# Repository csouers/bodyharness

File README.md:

# bodyharness
## Expand your openpilot experience with access to your vehicle's chassis CAN bus

Available for purchase at https://autofocuser.com!

This hardware, together with the necessary software and vehicle architecture, makes it possible to electronically control turn signals, door locks, and more. Future software will support features such as low fuel warnings, unlocked vehicle notifications, and headlights on during comma prime snapshots.

Currently, a comma.ai panda (white or grey) is the only required accessory. The black panda can be supported with additional effort (no plans for this at the moment). The supported pandas have 3 CAN bus transceivers, k-line and l-line connections, and a single GMLAN connection (operates in place of one of the panda's CAN bus connections). Future hardware revisions will support LIN (k-line and l-line).

## Compatibility
##### Based on vehicle generation. Vehicles may vary. Check your car first!
| Make | Model | B-CAN Connection Location |
| -- | -- | -- |
| Acura     | ILX 2016-18                   | TBD                                                                                          |
| Acura     | RDX 2016-18                   | TBD                                                                                          |
| Honda     | Accord 2018-21                | Option Connector (Pinout A) PINK 2+ / BLUE 3-                                                |
| Honda     | Accord Hybrid 2018-21         | Option Connector (Pinout A) PINK 2+ / BLUE 3-                                                |
| Honda     | Clarity 2017-21               | Option Connector (Pinout A) PINK 2+ / BLUE 3-                                                |
| Honda     | Civic Hatchback 2017-21       | Option Connector (Pinout A) PINK 2+ / BLUE 3-                                                |
| Honda     | Civic Sedan/Coupe 2016-21     | Option Connector (Pinout A) PINK 2+ / BLUE 3-                                                |
| Honda     | CR-V 2015-16                  | (DIY) at BCM/Under Dash Fuse Box or other module                                             |
| Honda     | CR-V 2017-21                  | Option Connector (Pinout A) PINK 2+ / BLUE 3-                                                |                                              
| Honda     | CR-V Hybrid 2017-2021         | Option Connector (Pinout A) PINK 2+ / BLUE 3-                                                |
| Honda     | Fit 2018-19                   | (DIY) 2018 at BCM/Under Dash Fuse/Relay Box or other module - 2019+ at ADAS Camera Connector |
| Honda     | HR-V 2019-2021                | (DIY) at ADAS Camera Connector                                                               |
| Honda     | Insight 2019-21               | (DIY) at BCM/Under Dash Fuse/Relay Box or other module                                       |
| Honda     | Odyssey 2018-21               | Option Connector (Pinout B) PINK 2+ / BLUE 5-                                                |
| Honda     | Passport 2019-21              | (DIY) BCM/Under Dash Fuse/Relay Box or other module - 2020+ at ADAS Camera Connector         |
| Honda     | Pilot 2016-21                 | (DIY) BCM/Under Dash Fuse/Relay or other module - 2019+ at ADAS Camera Connector             |
| Honda     | Ridgeline 2017-21             | (DIY) BCM/Under Dash Fuse/Relay or other module - 2020+ at ADAS Camera Connector             |

As usual, anything on this repository is to be used AT YOUR OWN RISK! You maintain all liability.
<!--stackedit_data:
eyJoaXN0b3J5IjpbMTAyMDg2MzIxNCw4MjI2NDQ3OTEsLTk1Nj
MwMjA3NiwtMTA4NjM2NzEwMiwxNDYwOTY0NjcxLDE2NzI0MDkw
NjIsLTE4NDM3OTQyNTAsLTIxNTEzMzYxMSwtMTEwMjgwNDYyNy
wxNTMyNDM0Mjk2XX0=
-->

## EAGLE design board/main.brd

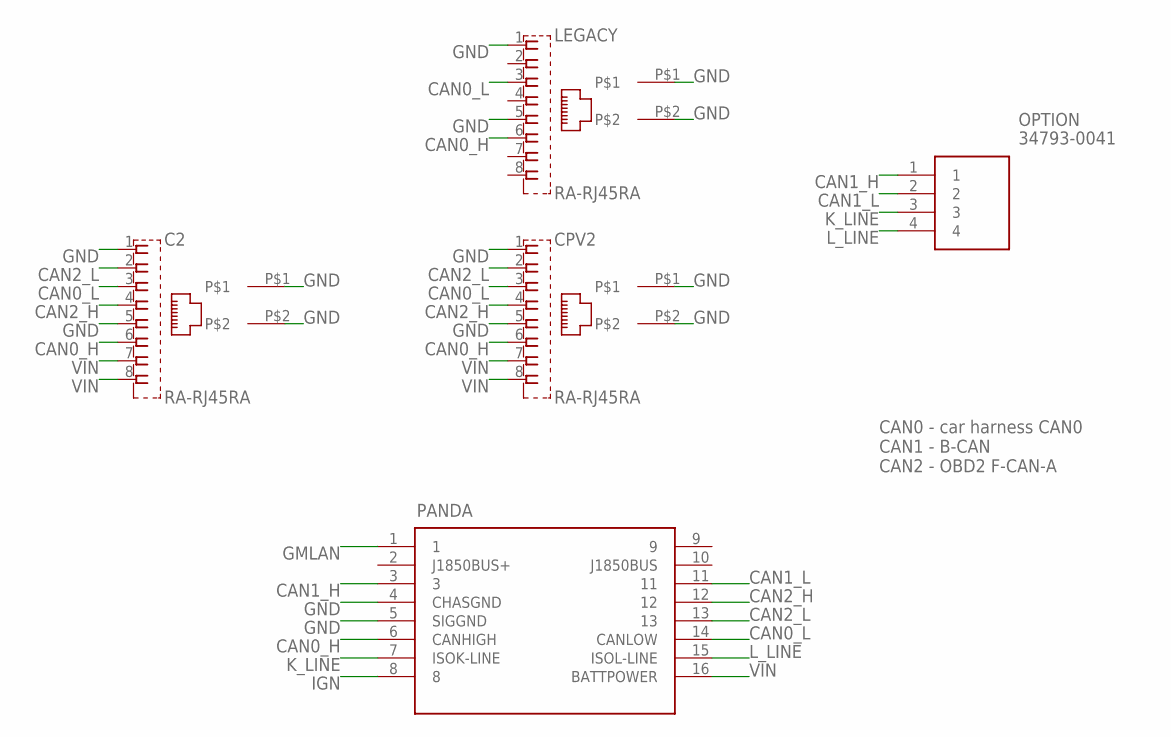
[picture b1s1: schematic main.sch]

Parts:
C2: RA-RJ45RA; RA-RJ45
CPV2: RA-RJ45RA; RA-RJ45
LEGACY: RA-RJ45RA; RA-RJ45
OPTION: 34793-0041; 347930041
PANDA: OBDII-FEMALEFEMALE; OBDII-FEMALE

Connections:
CAN0_H: C2.6, CPV2.6, LEGACY.6, PANDA.6 (CANHIGH)
CAN0_L: C2.3, CPV2.3, LEGACY.3, PANDA.14 (CANLOW)
CAN1_H: OPTION.1, PANDA.3
CAN1_L: OPTION.2, PANDA.11
CAN2_H: C2.4, CPV2.4, PANDA.12
CAN2_L: C2.2, CPV2.2, PANDA.13
GMLAN: PANDA.1
GND: C2.1, C2.5, C2.P$1, C2.P$2, CPV2.1, CPV2.5, CPV2.P$1, CPV2.P$2, LEGACY.1, LEGACY.5, LEGACY.P$1, LEGACY.P$2, PANDA.4 (CHASGND), PANDA.5 (SIGGND)
IGN: PANDA.8
K_LINE: OPTION.3, PANDA.7 (ISOK-LINE)
L_LINE: OPTION.4, PANDA.15 (ISOL-LINE)
VIN: C2.7, C2.8, CPV2.7, CPV2.8, PANDA.16 (BATTPOWER)

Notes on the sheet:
CAN0 - car harness CAN0 CAN1 - B-CAN CAN2 - OBD2 F-CAN-A

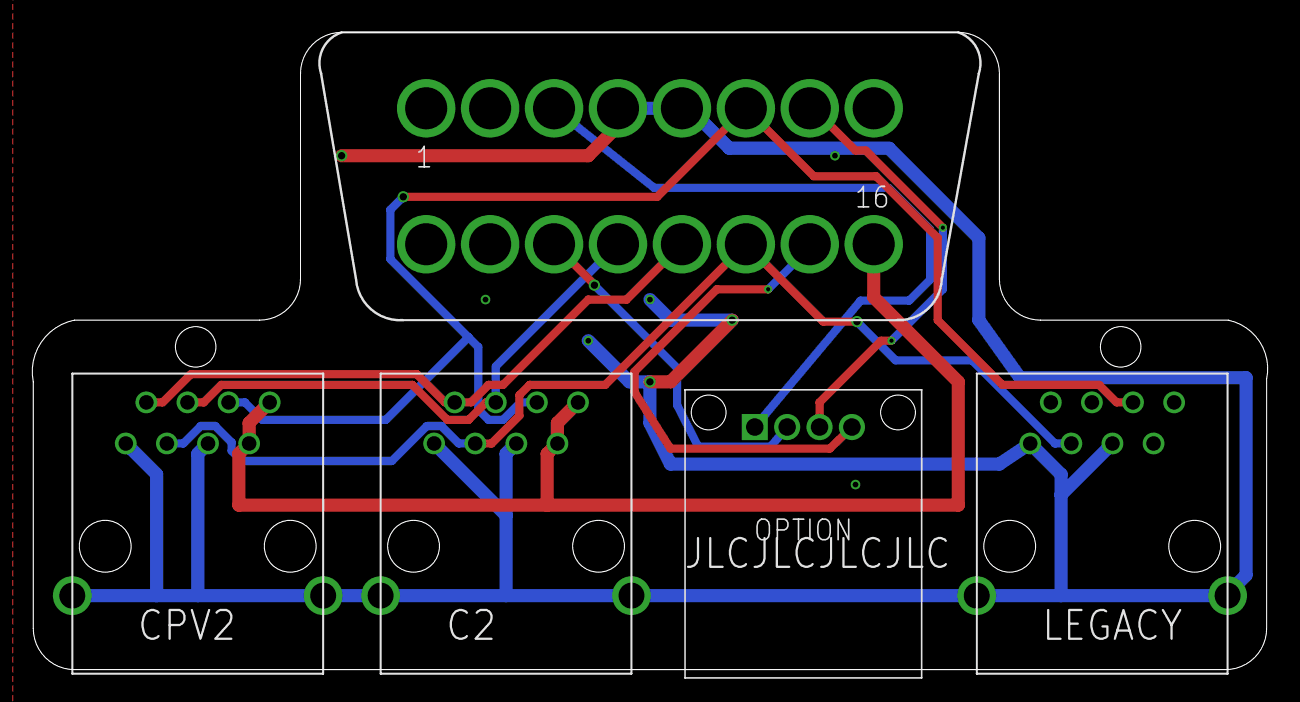
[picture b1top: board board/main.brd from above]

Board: 2 copper layers, 76.3 x 39.4 mm, 5 parts (0 on the bottom side), 10 nets.

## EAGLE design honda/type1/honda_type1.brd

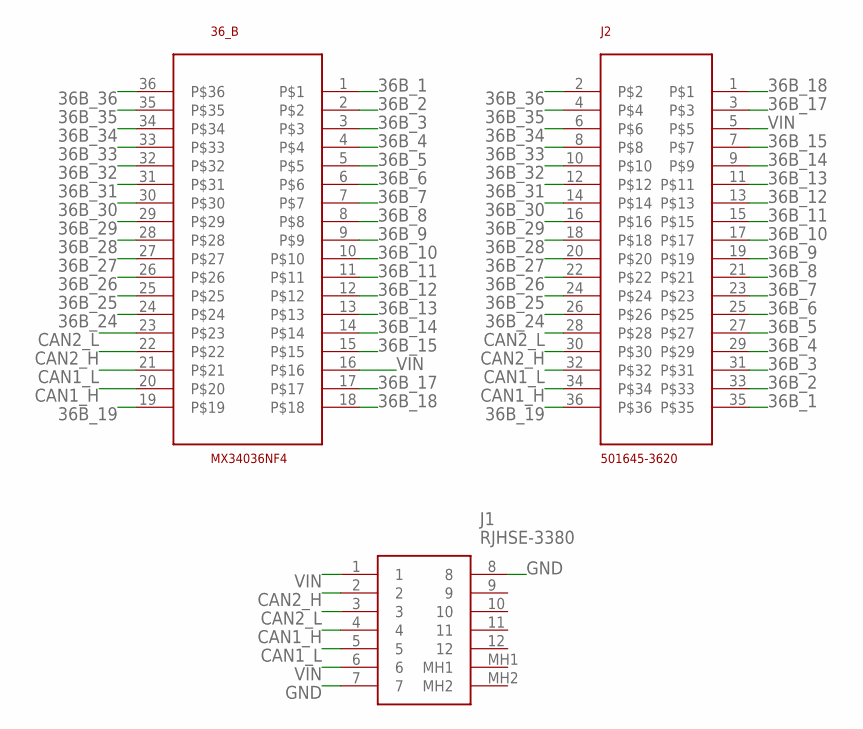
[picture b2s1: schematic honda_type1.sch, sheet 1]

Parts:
36_B: MX34036NF4; MX34036NF2
J1: RJHSE-3380; RJHSE3384
J2: 501645-3620

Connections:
36B_1: 36_B.1, J2.35
36B_2: 36_B.2, J2.33
36B_3: 36_B.3, J2.31
36B_4: 36_B.4, J2.29
36B_5: 36_B.5, J2.27
36B_6: 36_B.6, J2.25
36B_7: 36_B.7, J2.23
36B_8: 36_B.8, J2.21
36B_9: 36_B.9, J2.19
36B_10: 36_B.10, J2.17
36B_11: 36_B.11, J2.15
36B_12: 36_B.12, J2.13
36B_13: 36_B.13, J2.11
36B_14: 36_B.14, J2.9
36B_15: 36_B.15, J2.7
36B_17: 36_B.17, J2.3
36B_18: 36_B.18, J2.1
36B_19: 36_B.19, J2.36
36B_24: 36_B.24, J2.26
36B_25: 36_B.25, J2.24
36B_26: 36_B.26, J2.22
36B_27: 36_B.27, J2.20
36B_28: 36_B.28, J2.18
36B_29: 36_B.29, J2.16
36B_30: 36_B.30, J2.14
36B_31: 36_B.31, J2.12
36B_32: 36_B.32, J2.10
36B_33: 36_B.33, J2.8
36B_34: 36_B.34, J2.6
36B_35: 36_B.35, J2.4
36B_36: 36_B.36, J2.2
CAN1_H: 36_B.20, J1.4, J2.34
CAN1_L: 36_B.21, J1.5, J2.32
CAN2_H: 36_B.22, J1.2, J2.30
CAN2_L: 36_B.23, J1.3, J2.28
GND: J1.7, J1.8
VIN: 36_B.16, J1.1, J1.6, J2.5

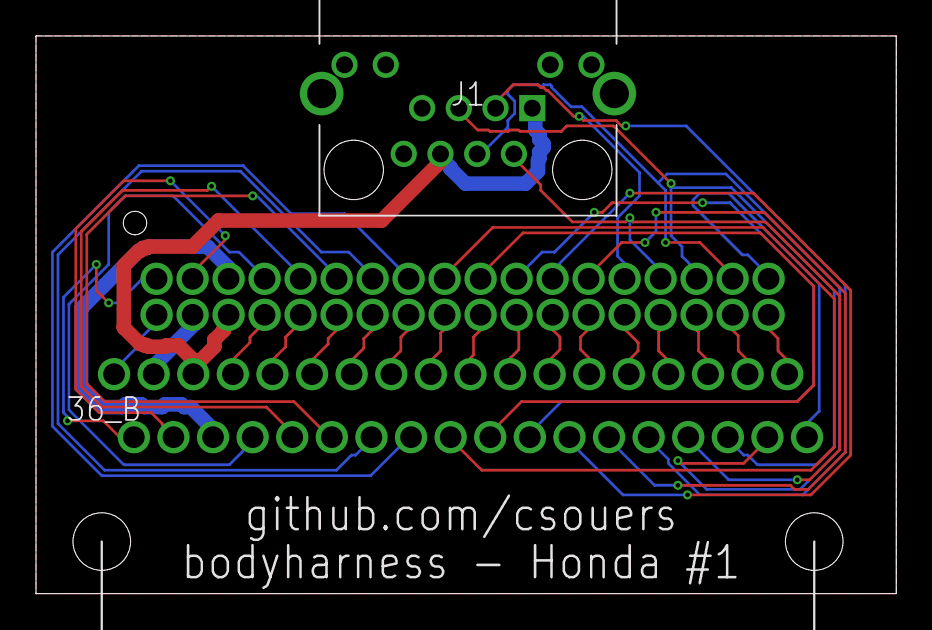
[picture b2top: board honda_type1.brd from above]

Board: 2 copper layers, 47.8 x 31.0 mm, 3 parts (1 on the bottom side), 37 nets.

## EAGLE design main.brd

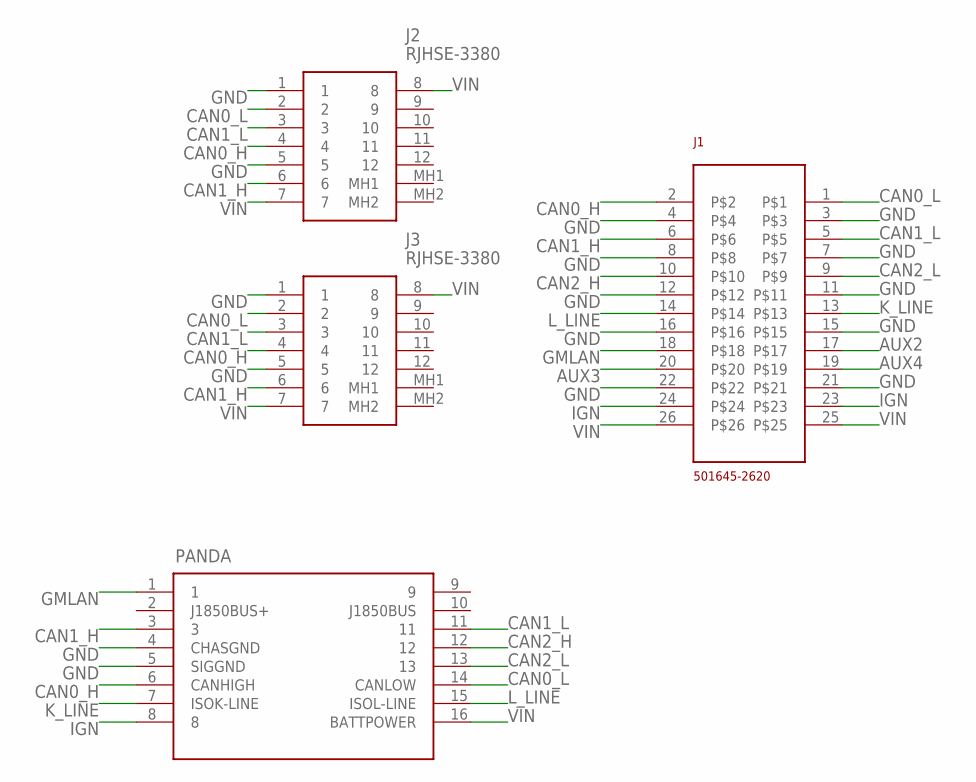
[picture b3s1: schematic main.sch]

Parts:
J1: 501645-2620
J2, J3: RJHSE-3380; RJHSE3384
PANDA: OBDII-FEMALEFEMALE; OBDII-FEMALE

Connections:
AUX2: J1.17
AUX3: J1.20
AUX4: J1.19
CAN0_H: J1.2, J2.4, J3.4, PANDA.6 (CANHIGH)
CAN0_L: J1.1, J2.2, J3.2, PANDA.14 (CANLOW)
CAN1_H: J1.6, J2.6, J3.6, PANDA.3
CAN1_L: J1.5, J2.3, J3.3, PANDA.11
CAN2_H: J1.10, PANDA.12
CAN2_L: J1.9, PANDA.13
GMLAN: J1.18, PANDA.1
GND: J1.3, J1.4, J1.7, J1.8, J1.11, J1.12, J1.15, J1.16, J1.21, J1.22, J2.1, J2.5, J3.1, J3.5, PANDA.4 (CHASGND), PANDA.5 (SIGGND)
IGN: J1.23, J1.24, PANDA.8
K_LINE: J1.13, PANDA.7 (ISOK-LINE)
L_LINE: J1.14, PANDA.15 (ISOL-LINE)
VIN: J1.25, J1.26, J2.7, J2.8, J3.7, J3.8, PANDA.16 (BATTPOWER)

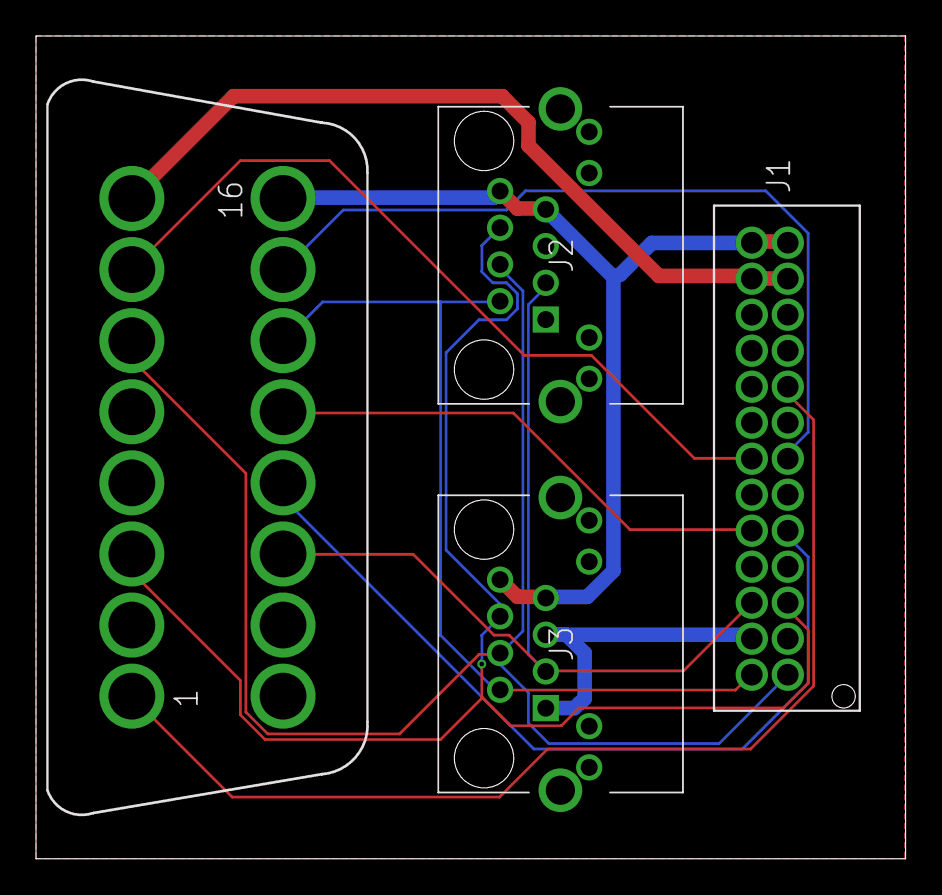
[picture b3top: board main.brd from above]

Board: 2 copper layers, 48.3 x 45.7 mm, 4 parts (0 on the bottom side), 12 nets.

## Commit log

2020-06-16 v0.1 of main
2020-06-18 README.md updated from https://stackedit.io/
2020-06-18 v0.2 of main
2020-07-01 push new versions. autorouted!
2020-07-01 organize. BOMs next commit
2020-07-01 rename
2020-07-02 switch to rj45 for the interconnect
2020-07-18 push
2020-08-12 add checksum info
2020-08-12 add some stuff that works and others that don't
2020-08-12 clean up
2020-08-13 move
2020-08-13 moving forward with a simplified setup
2020-08-19 main v2
2020-08-19 honda/honda.md updated from https://stackedit.io/
2020-08-19 upload production files
2020-11-03 Getting closer to release
2021-02-12 more images
2021-02-16 rev1.1c push and cleanup
2021-02-16 code changes and cleanup
2021-04-23 Update for 2021 models. Add Clarity.
